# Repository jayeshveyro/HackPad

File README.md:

# HackPad
I decided to build a Macropad for my first ever PCB project. This Hackpad consists of a Xiao RP2040 and 9 Cherry MX red switches. I will try to include for functionality in my next project of making a Keyboard.

## BOM(Bill of Materials)
| # | Component | SKU | Qty | Unit Price | Subtotal | Link |
|---|---|---:|---:|---:|---:|---|
| 1 | Seed Studio Xiao RP2040 |  1201742 | 1 | ₹579.00 | ₹579.00 | [Robu](https://robu.in/product/seeed-studio-xiao-rp2040-v1-0/) |
| 2 | Cherry MX Red switches | MX1A-L1NA | 1 | ₹375.00 | ₹375.00 | [Meckey](https://meckeys.com/shop/accessories/keyboard-accessories/key-switches/cherry-mx-rgb-switch/) |
| 3 | Lion Circuit PCB manufacturing | - | 1 | ₹1355.00 | ₹1355.00 | [Lion Circuit](https://www.lioncircuits.com/quote) |
| 4 | Printing Legion | - | 1 | ₹475.00 | ₹470.00 | [HackClub]() |
| | **TOTAL** | | | | **₹2779.00** | ||

## Schematics

## PCB

## 3D renders

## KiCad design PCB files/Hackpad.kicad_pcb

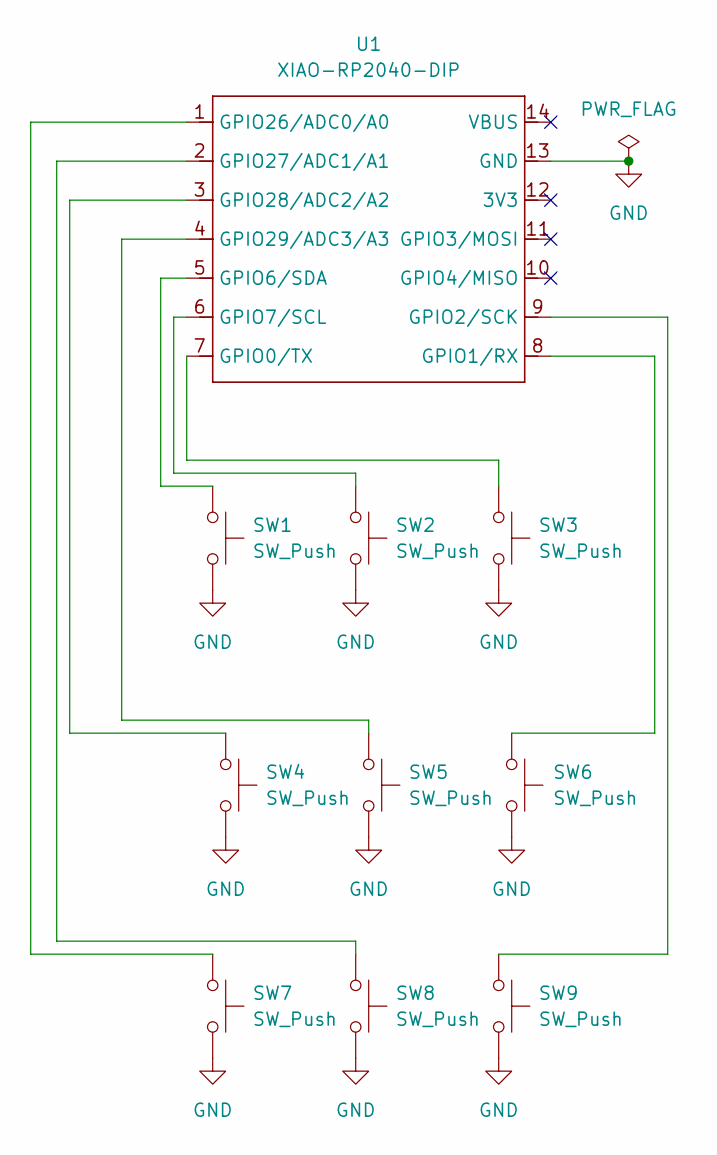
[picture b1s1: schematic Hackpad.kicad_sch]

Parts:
SW1, SW2, SW3, SW4, SW5, SW6, SW7, SW8, SW9: SW_Push; SW_Cherry_MX_1.00u_PCB
U1: XIAO-RP2040-DIP

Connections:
GND: SW1.2, SW2.2, SW3.2, SW4.2, SW5.2, SW6.2, SW7.2, SW8.2, SW9.2, U1.13 (GND)
unnamed: SW3.1, U1.7 (GPIO0/TX)
unnamed: SW6.1, U1.8 (GPIO1/RX)
unnamed: SW9.1, U1.9 (GPIO2/SCK)
unnamed: SW1.1, U1.5 (GPIO6/SDA)
unnamed: SW2.1, U1.6 (GPIO7/SCL)
unnamed: SW7.1, U1.1 (GPIO26/ADC0/A0)
unnamed: SW8.1, U1.2 (GPIO27/ADC1/A1)
unnamed: SW4.1, U1.3 (GPIO28/ADC2/A2)
unnamed: SW5.1, U1.4 (GPIO29/ADC3/A3)

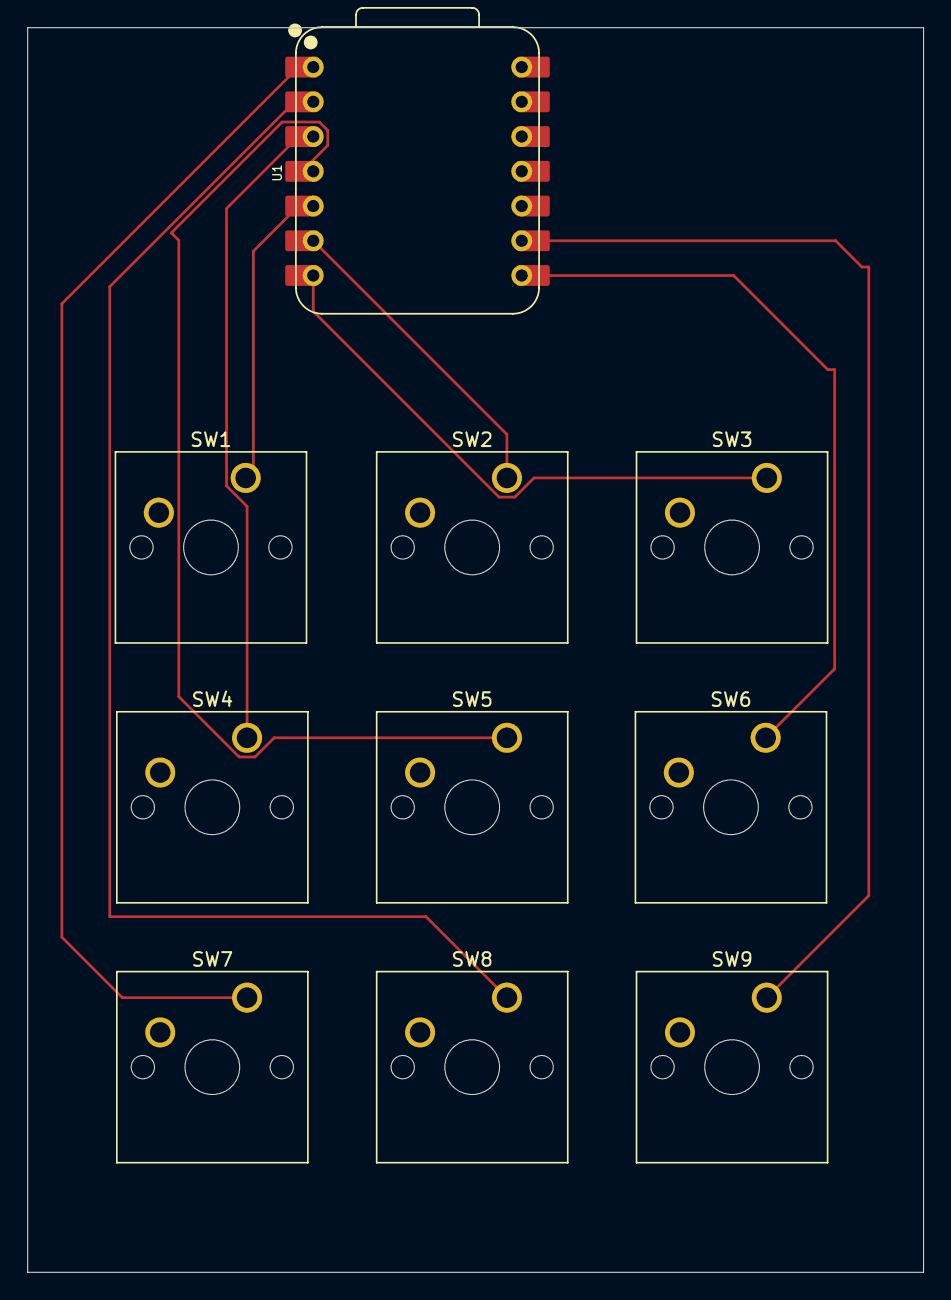
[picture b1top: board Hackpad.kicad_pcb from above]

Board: 2 copper layers, 65.5 x 91.0 mm, 10 parts (0 on the bottom side), 10 nets.
